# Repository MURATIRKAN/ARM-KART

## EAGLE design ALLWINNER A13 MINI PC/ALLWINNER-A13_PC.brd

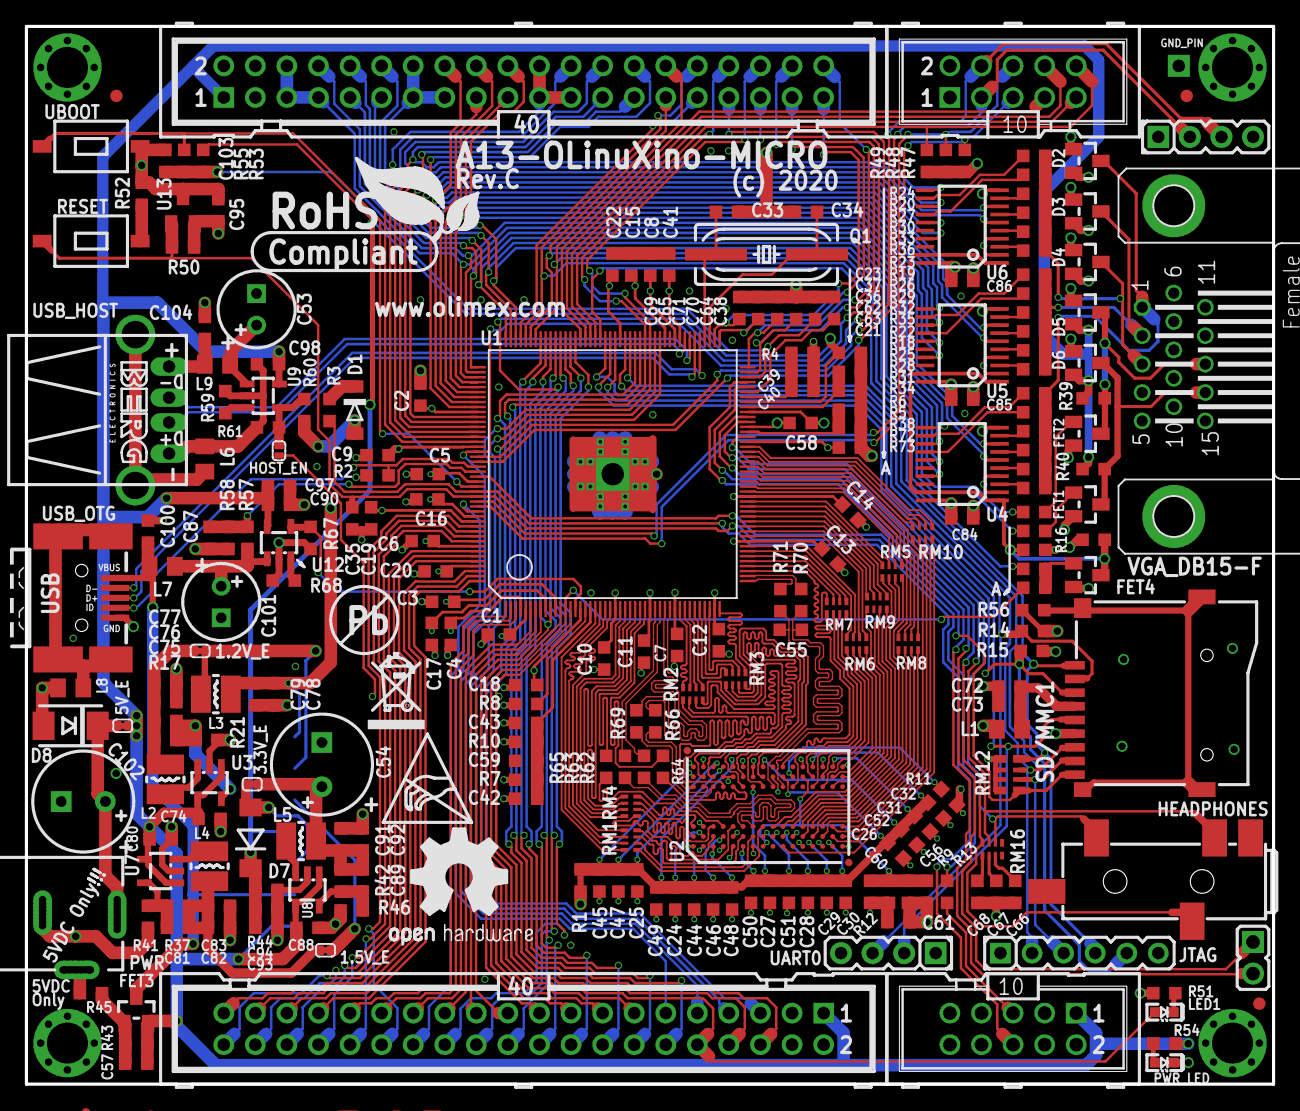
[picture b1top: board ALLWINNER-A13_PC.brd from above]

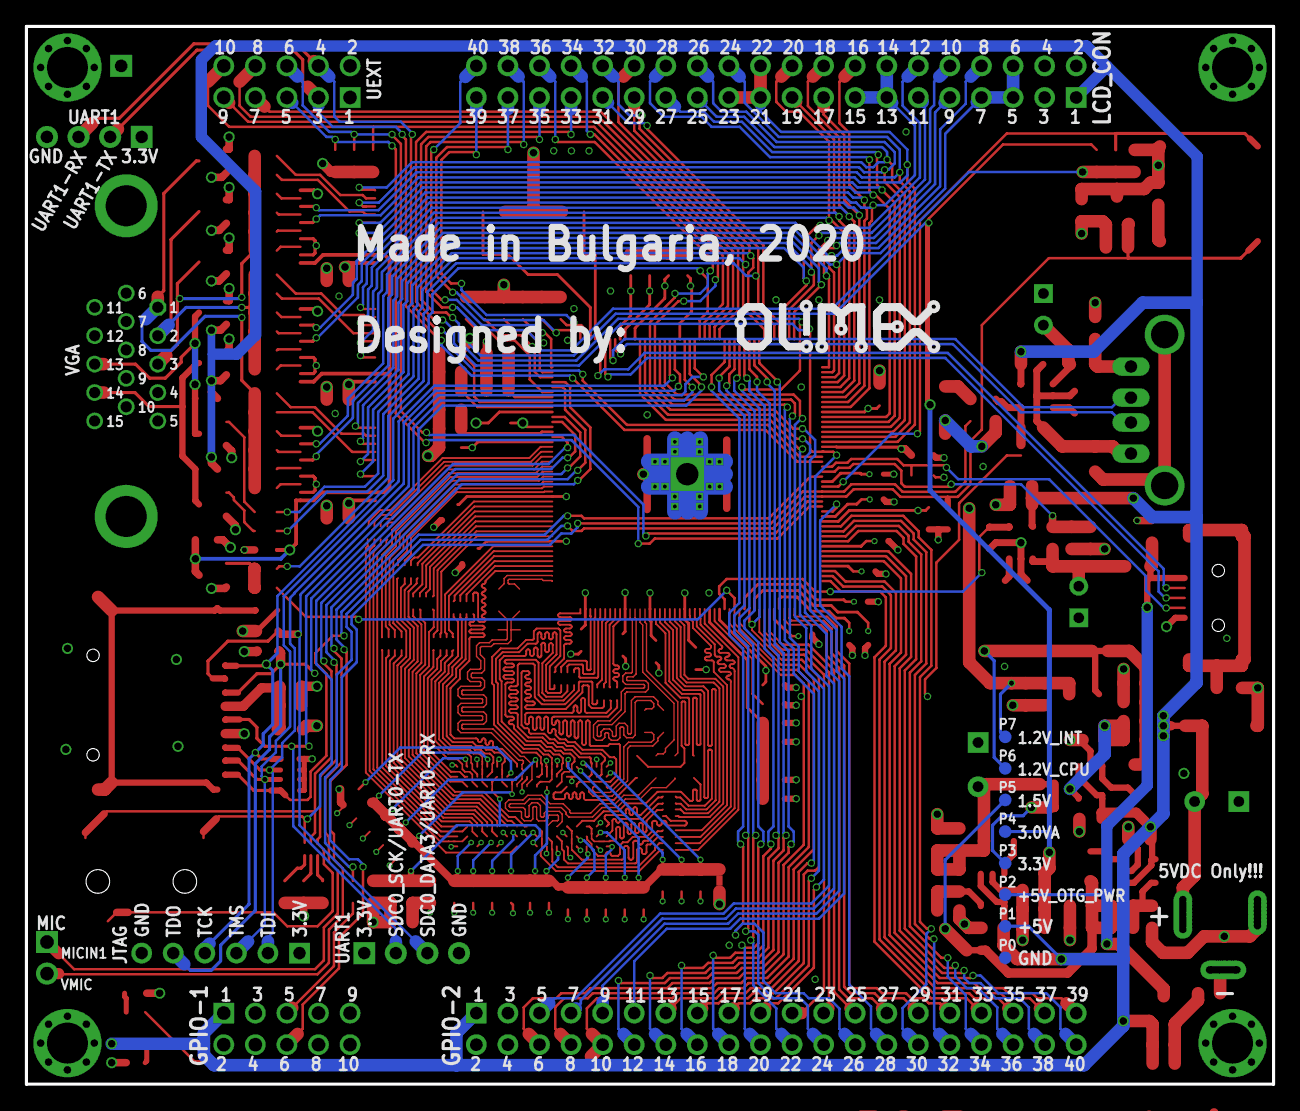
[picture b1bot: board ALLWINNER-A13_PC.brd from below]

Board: 4 copper layers, 100.3 x 85.1 mm, 261 parts (9 on the bottom side), 264 nets.

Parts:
1.2V_E, 1.5V_E, 3.3V_E, 5V_E: Close; SJ_1_SMALLER_CLOSE
C1, C11, C13, C15, C16, C17, C18, C19, C20, C21, C22, C24, C25, C26, C28, C29, C30, C31, C32, C37, C39, C41, C42, C43, C44, C45, C46, C47, C48, C49, C51, C52, C56, C57, C58, C59, C60, C63, C66, C67, C68, C84, C85, C86, C90, C95, C100, C104: 100nF; C0603_DWS
C2, C3, C7, C10, C23, C27, C50, C72, C73, C74, C76, C77, C80, C82, C83, C88, C91, C92, C93, C94, C97: 22uF/6.3V; C0603_DWS
C4, C5, C6, C8, C9, C12, C14, C36, C40, C62, C78, C98: 10uF/6.3V; C0603_DWS
C33, C34: 33pF; C0603_DWS
C35, C55: NA; C0603_DWS
C38: 1uF; C0603_DWS
C53, C101: 100uF/16V/LOWESR/105C/6.3x11mm_RM2.5; E2,5-6,3
C54: NA; E3,5-8
C61: NA(22uF/6.3V); C0603_DWS
C64, C65, C69, C70, C71, C79, C103: 1nF; C0603_DWS
C75, C81: 22pF; C0603_DWS
C87: NA(100nF); C0603_DWS
C89: 47pF; C0603_DWS
C102: 470uF/16V/105C; E3,5-8
D1: 1N5819(S4SOD-123); SOD-123
D2, D3, D4, D5, D6: BAT54S; SOT23C(BAT54S)
D7: 1N5819/SS14; MLL-41
D8: SMBJ6.0; DO214AA
FET1, FET2, FET4: BSS138; SOT23
FET3: IRLML6402; SOT23
GND_PIN: TESTPAD3; TEST_PAD40/70/SQUARE
GPIO-1: BH10S; ML10-MALE
GPIO-2: ML40
HEADPHONES: PJ-W47S-05D2-LF_V2; PJ-W47S-05D2-LF_5PIN_V2
HOST_EN: Open; SJ_1_SMALLER
JTAG: NA(HN1X6); HN1X6
L1, L6, L7, L8, L9: FB0805/600R/2A; L0805_5MIL_DWS
L2, L3, L4, L5: 2.2uH/1.5A/DCR<0.1R/CD32; CD32
LCD_CON: ML40
LED1: LED/GREEN/0603; LED-0603
MIC: NA(HN1x2); JP1
P0, P1, P2, P3, P4, P5, P6, P7: TESTPADTESTPAD_40-ROUND; TESTPAD_40-ROUND
PWR: YDJ-1136; PWR_JACK_UNI_MILLING
PWR_LED: LED/RED/0603; LED-0603
Q1: 24Mhz/HU49SM/20ppm/20pf; HC49/SMD2_THIN
R1: 0R(Board_Mounted); 0603_0R
R2, R3, R49, R57: 47k; R0603_5MIL_DWS
R4, R67: 200k/1%; R0603_5MIL_DWS
R5, R6, R52, R72: 51R; R0603_5MIL_DWS
R7, R10: 2k/1%; R0603_5MIL_DWS
R8, R11, R13: 240R/1%; R0603_5MIL_DWS
R9, R12, R16, R39, R40, R45: 1k/1%; R0603_5MIL_DWS
R14: NA(1M); R0603_5MIL_DWS
R15, R38, R43, R56, R60: 10k; R0603_5MIL_DWS
R17, R28, R29, R30: 2.2k/1%; R0603_5MIL_DWS
R18, R19, R20: 17.8k/1%; R0603_5MIL_DWS
R21: 1.5k/1%; R0603_5MIL_DWS
R22, R23, R24: 8.66k/1%; R0603_5MIL_DWS
R25, R26, R27: 4.32k/1%; R0603_5MIL_DWS
R31, R32, R33: 1.05k/1%; R0603_5MIL_DWS
R34, R35, R36: 549R/1%; R0603_5MIL_DWS
R37: 4.99k/1%; R0603_5MIL_DWS
R41: 3.3k/1%; R0603_5MIL_DWS
R42, R53, R58: 100k/1%; R0603_5MIL_DWS
R44, R47, R48, R51, R54: 2.2k; R0603_5MIL_DWS
R46: 22k/1%; R0603_5MIL_DWS
R50: 10k(NA); R0603_5MIL_DWS
R55: 6.8k/1%; R0603_5MIL_DWS
R59, R68: 13k/1%; R0603_5MIL_DWS
R61, R73: NA; R0603_5MIL_DWS
R62, R63, R64, R65, R66, R69, R70, R71: 22R; R0603_5MIL_DWS
RESET: T1107A(6x3.8x2.5mm); SW-TAKT_6X3.5_SMD
RM1, RM2, RM3, RM4, RM5, RM6, RM7, RM8, RM9, RM10, RM16: RA0805_(4X0402)_22R; R_MATRIX_4_0402_25X625
RM12: RA1206_(4X0603)_4B8_100K; R_MATRIX_4
SD/MMC1: MICRO_SD/TFC-WPAPR-08; TFC-WPAPR-08
U1: A13; TQFP176
U2: H5TQ2G63BFR; FBGA96@1
U3, U7, U8: SY8008C(AA)C; SOT23-5
U4, U5, U6: SN74ALVC244; PW
U9, U12: SY6280; SOT23-5
U13: MCP130T-300I/TT; SOT23
U$1, U$2, U$3: FIDUCIAL; FIDUCIAL-1X3
U$5: LOGO-OPENHARDWARE_8X8
U$8: OLIMEX1_V
U$9: PB
U$10: ESD_SYMBOL
U$11: RECYCLE_BIN1/8
U$12: ROHS
UART0: NA(HN1X4); HN1X4
UART1: HN1X4
UBOOT: T1107A(6x3.8x2.5mm); SW-TAKT_6X3.5_SMD
UEXT: BH10S; ML10-MALE
USB_HOST: USB_A; USB_PN87520_HOST_PTH
USB_OTG: USB-OTG; USB_MINI_9PIN
VGA_DB15-F: VGA15; DB15-F_22MM

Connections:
+5V: 5V_E.2, C57.1, C74.1, C80.1, C88.1, C90.1, C97.1, C98.1, D5.2, D6.2, FET3.2, GPIO-1.1, GPIO-2.1, LCD_CON.1, P1.1, R39.2, R40.2, R43.2, R54.1, U3.1, U3.4, U7.1, U7.4, U8.1, U8.4, U9.5, U12.5
+5V_OTG_PWR: C100.1, FET3.3, L7.1, P2.1, USB_OTG.VBUS
A0: RM5.1.2, U2.N3
A1: RM6.3.2, U2.P7
A2: RM8.3.2, U2.P3
A3: RM8.4.2, U2.N2
A4: RM6.4.2, U2.P8
A5: RM8.2.2, U2.P2
A6: RM6.2.2, U2.R8
A7: RM10.2.2, U2.R2
A8: RM6.1.2, U2.T8
A9: RM10.4.2, U2.R3
A10: RM7.3.2, U2.L7
A11: RM9.4.2, U2.R7
A12: RM7.1.2, U2.N7
A13: RM8.1.2, U2.T3
BA0: RM5.2.2, U2.M2
BA1: RM7.2.2, U2.N8
BA2: RM5.3.2, U2.M3
CASN: RM9.1.2, U2.K3
CKE: RM7.4.2, U2.K9
CLK: C55.1, R71.1, U2.J7
CLKN: C55.2, R70.1, U2.K7
D0: RM1.1.2, U2.E3
D1: RM3.4.2, U2.F7
D2: RM1.2.2, U2.F2
D3: RM3.3.2, U2.F8
D4: RM1.4.2, U2.H3
D5: RM3.1.2, U2.H8
D6: RM1.3.2, U2.G2
D7: RM3.2.2, U2.H7
D8: RM2.3.2, U2.D7
D9: RM4.3.2, U2.C3
D10: RM2.1.2, U2.C8
D11: RM4.4.2, U2.C2
D12: RM2.4.2, U2.A7
D13: RM4.2.2, U2.A2
D14: RM2.2.2, U2.B8
D15: RM4.1.2, U2.A3
DDR3_A0: RM5.1.1, U1.64
DDR3_A1: RM6.3.1, U1.52
DDR3_A2: RM8.3.1, U1.66
DDR3_A3: RM8.4.1, U1.65
DDR3_A4: RM6.4.1, U1.51
DDR3_A5: RM8.2.1, U1.67
DDR3_A6: RM6.2.1, U1.54
DDR3_A7: RM10.2.1, U1.71
DDR3_A8: RM6.1.1, U1.55
DDR3_A9: RM10.4.1, U1.69
DDR3_A10: RM7.3.1, U1.48
DDR3_A11: RM9.4.1, U1.56
DDR3_A12: RM7.1.1, U1.50
DDR3_A13: RM8.1.1, U1.68
DDR3_A14: RM9.3.1, U1.57
DDR3_BA0: RM5.2.1, U1.63
DDR3_BA1: RM7.2.1, U1.49
DDR3_BA2: RM5.3.1, U1.61
DDR3_CAS: RM9.1.1, U1.59
DDR3_CK: R71.2, U1.45
DDR3_CKE: RM7.4.1, U1.47
DDR3_CK_N: R70.2, U1.46
DDR3_D0: RM1.1.1, U1.22
DDR3_D1: RM3.4.1, U1.40
DDR3_D2: RM1.2.1, U1.21
DDR3_D3: RM3.3.1, U1.41
DDR3_D4: RM1.4.1, U1.19
DDR3_D5: RM3.1.1, U1.44
DDR3_D6: RM1.3.1, U1.20
DDR3_D7: RM3.2.1, U1.42
DDR3_D8: RM2.3.1, U1.37
DDR3_D9: RM4.3.1, U1.25
DDR3_D10: RM2.1.1, U1.39
DDR3_D11: RM4.4.1, U1.24
DDR3_D12: RM2.4.1, U1.36
DDR3_D13: RM4.2.1, U1.26
DDR3_D14: RM2.2.1, U1.38
DDR3_D15: RM4.1.1, U1.27
DDR3_DM0: R64.2, U1.29
DDR3_DM1: R65.2, U1.28
DDR3_DQS0: R63.2, U1.31
DDR3_DQS0_N: R62.2, U1.32
DDR3_DQS1: R69.2, U1.33
DDR3_DQS1_N: R66.2, U1.34
DDR3_ODT: RM10.1.2, U2.K1
DDR3_ODTT: RM10.1.1, U1.72
DDR3_RAS: RM9.2.1, U1.58
DDR3_RST: RM10.3.2, U2.T2
DDR3_RSTT: RM10.3.1, U1.70
DDR3_WE: RM5.4.1, U1.60
DQM0: R64.1, U2.E7
DQM1: R65.1, U2.D3
DQS0: R63.1, U2.F3
DQS0_N: R62.1, U2.G3
DQS1: R69.1, U2.C7
DQS1_N: R66.1, U2.B7
DZQ: R8.2, U1.17
GND: C1.1, C2.1, C3.1, C4.1, C5.1, C6.1, C7.1, C8.1, C9.1, C10.1, C11.1, C12.1, C13.1, C14.1, C15.1, C16.1, C17.1, C18.1, C19.1, C20.1, C21.1, C22.1, C23.1, C24.2, C25.2, C26.2, C27.2, C28.2, C29.2, C30.2, C31.2, C32.2, C33.1, C34.1, C35.1, C36.1, C37.1, C38.1, C39.1, C40.1, C41.1, C43.1, C44.2, C45.2, C46.2, C47.2, C48.2, C49.2, C50.2, C51.2, C52.2, C53.-, C54.-, C58.1, C59.1, C60.1, C61.1, C62.1, C63.1, C64.1, C65.1, C66.1, C67.1, C68.1, C69.1, C70.1, C71.1, C72.1, C73.1, C74.2, C76.2, C77.2, C78.2, C79.2, C80.2, C82.2, C83.2, C84.2, C85.2, C86.2, C87.2, C88.2, C90.2, C91.2, C92.2, C93.2, C94.2, C95.2, C97.2, C98.2, C100.2, C101.-, C102.-, C103.2, C104.2, D2.1, D3.1, D4.1, D5.1, D6.1, D8.A, FET1.2, FET2.2, FET4.2, GND_PIN.P$1, GPIO-1.2, GPIO-1.4, GPIO-2.2, GPIO-2.4, JTAG.6, L6.1, L8.1, LCD_CON.2, LCD_CON.4, P0.1, PWR.-, PWR_LED.C, R4.2, R8.1, R10.1, R11.1, R12.1, R14.2, R21.2, R38.1, R41.2, R44.2, R46.2, R51.1, R52.2, R56.2, R58.1, R59.1, R61.1, R67.1, R68.1, SD/MMC1.6, U1.79, U1.GND_PAD, U1.P$2, U1.P$3, U1.P$4, U1.P$5, U1.P$6, U1.P$7, U1.P$8, U1.P$9, U1.P$10, U1.P$11, U1.P$12, U1.P$13, U1.P$14, U1.P$15, U1.P$16, U1.P$17, U1.P$18, U2.A9, U2.B1, U2.B3, U2.B9, U2.D1, U2.D8, U2.E1, U2.E2, U2.E8, U2.F9, U2.G1, U2.G8, U2.G9, U2.J2, U2.J8, U2.L2, U2.M1, U2.M9, U2.P1, U2.P9, U2.T1, U2.T9, U3.2, U4.2, U4.4, U4.10, U5.2, U5.4, U5.10, U6.2, U6.4, U6.10, U7.2, U8.2, U9.2, U12.2, U13.3, UART0.4, UART1.4, UBOOT.P$1, UEXT.2, USB_HOST.4, USB_OTG.GND, VGA_DB15-F.5, VGA_DB15-F.6, VGA_DB15-F.7, VGA_DB15-F.8, VGA_DB15-F.10, VGA_DB15-F.GND1, VGA_DB15-F.GND2
LCD_CLK: LCD_CON.31, U1.129
LCD_D2: LCD_CON.21, LCD_CON.22, LCD_CON.23, U1.148, U6.6
LCD_D3: LCD_CON.24, U1.147, U6.8
LCD_D4: LCD_CON.25, U1.146, U6.11
LCD_D5: LCD_CON.26, U1.145, U6.13
LCD_D6: LCD_CON.27, U1.144, U6.15
LCD_D7: LCD_CON.28, U1.143, U6.17
LCD_D10: LCD_CON.13, LCD_CON.14, LCD_CON.15, U1.141, U5.6
LCD_D11: LCD_CON.16, U1.140, U5.8
LCD_D12: LCD_CON.17, U1.139, U5.11
LCD_D13: LCD_CON.18, U1.138, U5.13
LCD_D14: LCD_CON.19, U1.137, U5.15
LCD_D15: LCD_CON.20, U1.136, U5.17
LCD_D18: LCD_CON.5, LCD_CON.6, LCD_CON.7, U1.135, U4.6
LCD_D19: LCD_CON.8, U1.134, U4.8
LCD_D20: LCD_CON.9, U1.133, U4.11
LCD_D21: LCD_CON.10, U1.132, U4.13
LCD_D22: LCD_CON.11, U1.131, U4.15
LCD_D23: LCD_CON.12, U1.130, U4.17
LCD_DE: LCD_CON.32, R72.2, U1.128
LCD_HSYNC: LCD_CON.29, R6.1, U1.127
LCD_VSYNC: LCD_CON.30, R5.1, U1.126
LRADC: C64.2, C103.1, R53.2, R55.1, U1.86
MICIN1: MIC.1, U1.84
unnamed: C62.2, C63.2, U1.75
unnamed: FET4.1, R72.1, R73.1
unnamed: 5V_E.1, C102.+, D8.C, PWR.+
unnamed: L2.1, U3.3
unnamed: R56.1, SD/MMC1.10, SD/MMC1.11, SD/MMC1.12, SD/MMC1.13
unnamed: C57.2, FET3.1, R43.1, R45.2
unnamed: L4.1, U7.3
unnamed: C36.2, C37.2, U1.80
unnamed: D1.C, R3.2
unnamed: PWR.--, R45.1
unnamed: FET1.1, R5.2
unnamed: C38.2, U1.83
unnamed: C39.2, C40.2, R4.1, U1.82
unnamed: FET2.1, R6.2
unnamed: C101.+, L7.2, R57.2, U12.1
unnamed: 1.5V_E.1, C81.1, C82.1, C83.1, L4.2, R37.1
unnamed: C81.2, R37.2, R41.1, U7.5
unnamed: R33.1, U6.5
unnamed: L6.2, USB_HOST.P$1, USB_HOST.P$2
unnamed: 1.2V_E.1, C75.1, C76.1, C77.1, L2.2, R17.1
unnamed: HOST_EN.2, R60.2, R61.2, U9.4
unnamed: HEADPHONES.2, RM16.3.2, U1.74
unnamed: HEADPHONES.5, RM16.2.2, U1.77
unnamed: HEADPHONES.3, RM16.1.2, U1.78
unnamed: C66.2, RM16.3.1
unnamed: C67.2, RM16.2.1
unnamed: GPIO-1.5, R13.2
unnamed: C56.2, C60.2, R9.1, R12.2, U2.H1, U2.M8
unnamed: C75.2, R17.2, R21.1, U3.5
unnamed: LED1.C, R51.2
unnamed: C68.2, RM16.1.1
unnamed: R52.1, RESET.P$1
unnamed: L5.1, U8.3
unnamed: 3.3V_E.1, C54.+, C89.1, C91.1, C92.1, L5.2, R42.1
unnamed: C89.2, R42.2, R46.1, U8.5
unnamed: R68.2, U12.3
unnamed: R59.2, U9.3
unnamed: R36.1, U6.3
unnamed: R27.1, U6.9
unnamed: R30.1, U6.7
unnamed: R20.1, U6.14
unnamed: R24.1, U6.12
unnamed: C104.1, L9.2, USB_HOST.1
unnamed: C53.+, L9.1, U9.1
unnamed: R26.1, U5.9
unnamed: R29.1, U5.7
unnamed: PWR_LED.A, R54.2
unnamed: R32.1, U5.5
unnamed: R35.1, U5.3
unnamed: R19.1, U5.14
unnamed: R23.1, U5.12
unnamed: R25.1, U4.9
unnamed: R28.1, U4.7
unnamed: R31.1, U4.5
unnamed: R34.1, U4.3
unnamed: R18.1, U4.14
unnamed: R22.1, U4.12
unnamed: L8.2, USB_OTG.GND1, USB_OTG.GND2, USB_OTG.GND3, USB_OTG.GND4
NMI_N: GPIO-1.6, R3.1, U1.158
PIN4/TWI0-SCK: GPIO-2.5, U1.101
PIN5/TWI0-SDA: GPIO-2.7, U1.102
PIN6/PWM0: GPIO-2.9, LCD_CON.36, U1.103
PIN7: GPIO-2.11, LCD_CON.33, U1.150
PIN8: GPIO-2.13, LCD_CON.34, U1.104
PIN9: GPIO-2.15, LCD_CON.35, U1.10
PIN10/TWI1-SCK: GPIO-2.17, U1.105
PIN11/TWI1-SDA: GPIO-2.19, U1.106
PIN12/NWE: GPIO-2.21, U1.8
PIN13/NALE: GPIO-2.23, U1.7
PIN14/NCLE: GPIO-2.25, U1.6
PIN15/NCE1: GPIO-2.27, U1.3
PIN16/NCE0: GPIO-2.29, U1.2
PIN17/NRE: GPIO-2.31, U1.1
PIN18/NRB0: GPIO-2.33, U1.176
PIN19/NRB1: GPIO-2.35, U1.175
PIN20/NDQ0: GPIO-2.37, U1.174
PIN21/NDQ1: GPIO-2.39, U1.172
PIN22/NDQ2: GPIO-2.40, U1.171
PIN23/NDQ3: GPIO-2.38, U1.170
PIN24/NDQ4: GPIO-2.36, U1.168
PIN25/NDQ5: GPIO-2.34, U1.167
PIN26/NDQ6: GPIO-2.32, U1.166
PIN27/NDQ7: GPIO-2.30, U1.165
PIN28/NDQS: GPIO-2.28, U1.162
PIN29: GPIO-2.26, U1.118
PIN30: GPIO-2.24, U1.119
PIN31: GPIO-2.22, U1.120
PIN32: GPIO-2.20, U1.121
PIN33: GPIO-2.18, U1.122
PIN34: GPIO-2.16, U1.123
PIN35: GPIO-2.14, U1.124
PIN36: GPIO-2.12, U1.125
PIN37/LED1: GPIO-2.10, LED1.A, U1.12
PIN38/VGA_DIS: GPIO-2.8, R73.2, U1.13
PIN39/USBH_EN: GPIO-2.6, HOST_EN.1, U1.14
RASN: RM9.2.2, U2.J3
RESET_N: C35.2, R13.1, R50.1, RESET.P$2, U1.159, U13.1
SD0CARD-DETECT: RM12.1.1, SD/MMC1.9, U1.155
SDC0_CMD: JTAG.5, R15.1, SD/MMC1.3, U1.111
SDC0_DATA0: JTAG.2, RM12.3.1, SD/MMC1.7, U1.108
SDC0_DATA1: JTAG.3, RM12.2.1, SD/MMC1.8, U1.107
SDC0_DATA2: JTAG.4, RM12.4.1, SD/MMC1.1, U1.113
SDC0_DATA3: R14.1, SD/MMC1.2, U1.112, UART0.3
SDC0_SCK: SD/MMC1.5, U1.110, UART0.2
SD_VCC: C72.2, C73.2, L1.2, SD/MMC1.4
SPI2_CLK: U1.115, UEXT.9
SPI2_CS0: R49.1, U1.114, UEXT.10
SPI2_MISO: U1.117, UEXT.7
SPI2_MOSI: U1.116, UEXT.8
SVREF: C42.2, C43.2, C59.2, R7.1, R10.2, U1.18
TPX1: C65.2, LCD_CON.37, U1.89
TPX2: C70.2, LCD_CON.38, U1.87
TPY1: C69.2, LCD_CON.39, U1.90
TPY2: C71.2, LCD_CON.40, U1.88
TWI2_SCK: R47.1, U1.161, UEXT.5
TWI2_SDA: R48.1, U1.160, UEXT.6
UART1_RX: U1.151, UART1.3, UEXT.4
UART1_TX: U1.152, UART1.2, UEXT.3
UBOOT: R55.2, U1.157, UBOOT.P$2
UDM0: U1.93, USB_OTG.D-
UDM1: U1.95, USB_HOST.2
UDP0: U1.94, USB_OTG.D+
UDP1: U1.96, USB_HOST.3
USB0-DRV: R67.2, U1.15, U12.4
USB0-IDDET: R2.2, U1.153, USB_OTG.ID
USB0-VBUSDET: C87.1, R57.1, R58.2, U1.154
V+: 1.5V_E.2, C10.2, C11.2, C12.2, C13.2, C14.2, C42.1, C56.1, C61.2, P5.1, R1.1, R7.2, R9.2, U1.23, U1.30, U1.43, U1.53, U1.62
VCC: 3.3V_E.2, C1.2, C2.2, C15.2, C16.2, C41.2, C58.2, C84.1, C85.1, C86.1, C95.1, D1.A, D2.2, D3.2, D4.2, D7.A, GPIO-1.3, GPIO-2.3, JTAG.1, L1.1, LCD_CON.3, P3.1, R2.1, R15.2, R16.2, R47.2, R48.2, R49.2, R50.2, R60.1, RM12.1.2, RM12.2.2, RM12.3.2, RM12.4.2, U1.5, U1.76, U1.97, U1.100, U1.142, U1.163, U4.20, U5.20, U6.20, U13.2, UART0.1, UART1.1, UEXT.1
VCC/2: 1.2V_E.2, C3.2, C4.2, C5.2, C6.2, C17.2, C18.2, C19.2, C20.2, L3.1, P6.1, U1.4, U1.9, U1.11, U1.16, U1.156, U1.164, U1.169, U1.173
VCCINT: C7.2, C8.2, C9.2, C21.2, C22.2, C78.1, C79.1, L3.2, P7.1, U1.35, U1.73, U1.98, U1.109, U1.149
VDD.: C24.1, C25.1, C26.1, C27.1, C28.1, C29.1, C30.1, C31.1, C32.1, C44.1, C45.1, C46.1, C47.1, C48.1, C49.1, C50.1, C51.1, C52.1, R1.2, U2.A1, U2.A8, U2.B2, U2.C1, U2.C9, U2.D2, U2.D9, U2.E9, U2.F1, U2.G7, U2.H2, U2.H9, U2.K2, U2.K8, U2.N1, U2.N9, U2.R1, U2.R9
VGA_B: D4.3, R20.2, R24.2, R27.2, R30.2, R33.2, R36.2, VGA_DB15-F.3
VGA_CTRL: FET4.3, R16.1, R38.2, U4.1, U4.19, U5.1, U5.19, U6.1, U6.19
VGA_G: D3.3, R19.2, R23.2, R26.2, R29.2, R32.2, R35.2, VGA_DB15-F.2
VGA_HSYNC: D5.3, FET2.3, R39.1, VGA_DB15-F.13
VGA_R: D2.3, R18.2, R22.2, R25.2, R28.2, R31.2, R34.2, VGA_DB15-F.1
VGA_VSYNC: D6.3, FET1.3, R40.1, VGA_DB15-F.14
VMIC: MIC.2, U1.85
VPP: C23.2, C93.1, C94.1, D7.K, P4.1, R44.1, R53.1, U1.81
WEN: RM5.4.2, U2.L3
XTALI: C33.2, Q1.2, U1.92
XTALO: C34.2, Q1.1, U1.91
ZQ: R11.2, U2.L8

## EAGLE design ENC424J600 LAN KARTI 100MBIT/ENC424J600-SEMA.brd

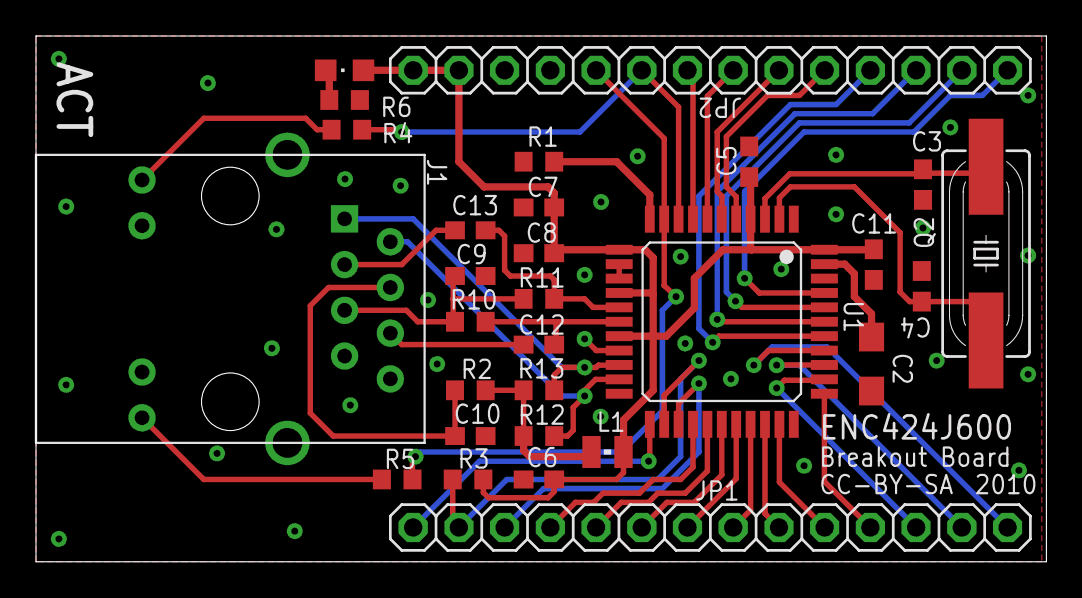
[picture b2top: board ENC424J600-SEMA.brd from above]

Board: 2 copper layers, 56.1 x 29.2 mm, 30 parts (1 on the bottom side), 42 nets.

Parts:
C2: 10uF; SMC_A
C3, C4: 27pf; C0603
C5, C6, C7, C8, C11: 0.1uF; C0603
C9, C10: 0.01uF; C0603
C12, C13: 6.8nF; C0603
J1: HR911105A
JP1, JP2: 1X14
L1: WE-KI_0805_B
PWR: LED-805
Q2: 25Mhz; HC49UP
R1: 12.4K 1%; R0603
R2: 10R, 1/12W, 1%; R0603
R3: 100K; R0603
R4, R5: 1K1; R0603
R6: 1k1; R0603
R10, R11, R12, R13: 49R9 1%; R0603
U1: ENC424J600; TQFP44
U$2: DP_LOGO

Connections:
3V3: C5.1, C6.1, C7.1, C8.1, C11.1, JP2.1, JP2.2, L1.1, PWR.A, R3.1, U1.P4, U1.P12, U1.P15, U1.P18, U1.P44
ACTIVITY: J1.9, R4.2
AD0: JP2.11, U1.P38
AD1: JP2.12, U1.P39
AD2: JP2.13, U1.P40
AD3: JP2.14, U1.P41
AD4: JP2.10, U1.P5
AD5: JP2.9, U1.P6
AD6: JP2.8, U1.P7
AD7: JP2.7, U1.P8
AD8: JP1.3, U1.P25
AD9: JP1.4, U1.P26
AD10: JP1.5, U1.P27
AD11: JP1.6, U1.P28
AD12: JP1.7, U1.P29
AD13: JP1.8, U1.P30
AD14: JP1.9, U1.P31
CCT: L1.2, R2.1, R12.2, R13.2
CLKOUT: JP1.1, U1.P23
DSFGDF: C12.1, R10.1, U1.P17
DSGDFSG: C13.1, R11.1, U1.P16
ETH-CS: JP1.11, U1.P34
ETH-INT: JP1.2, R3.2, U1.P24
ETH-MISO: JP1.12, U1.P35
ETH-MOSI: JP1.13, U1.P36
ETH-SCK: JP1.14, U1.P37
GND: C2.-, C3.2, C4.2, C5.2, C6.2, C7.2, C8.2, C9.2, C10.2, C11.2, J1.10, J1.11, J1.13, J1.14, JP2.3, JP2.4, R1.2, R6.1, U1.P1, U1.P13, U1.P14, U1.P19, U1.P22, U1.P33, U1.P42
LED_A: JP2.5, R5.1, U1.P10
LED_B: JP2.6, R4.1, U1.P9
LINK: J1.12, R5.2
unnamed: C2.+, U1.P43
unnamed: R1.1, U1.P11
unnamed: PWR.C, R6.2
unnamed: C3.1, Q2.1, U1.P3
unnamed: C4.1, Q2.2, U1.P2
PSPCFG0: JP1.10, U1.P32
RD+: C13.2, J1.3
RD-: C12.2, J1.6
RD-CT: C9.1, J1.5, R10.2, R11.2
TD+: J1.1, R13.1, U1.P20
TD-: J1.2, R12.1, U1.P21
TD-CT: C10.1, J1.4, R2.2

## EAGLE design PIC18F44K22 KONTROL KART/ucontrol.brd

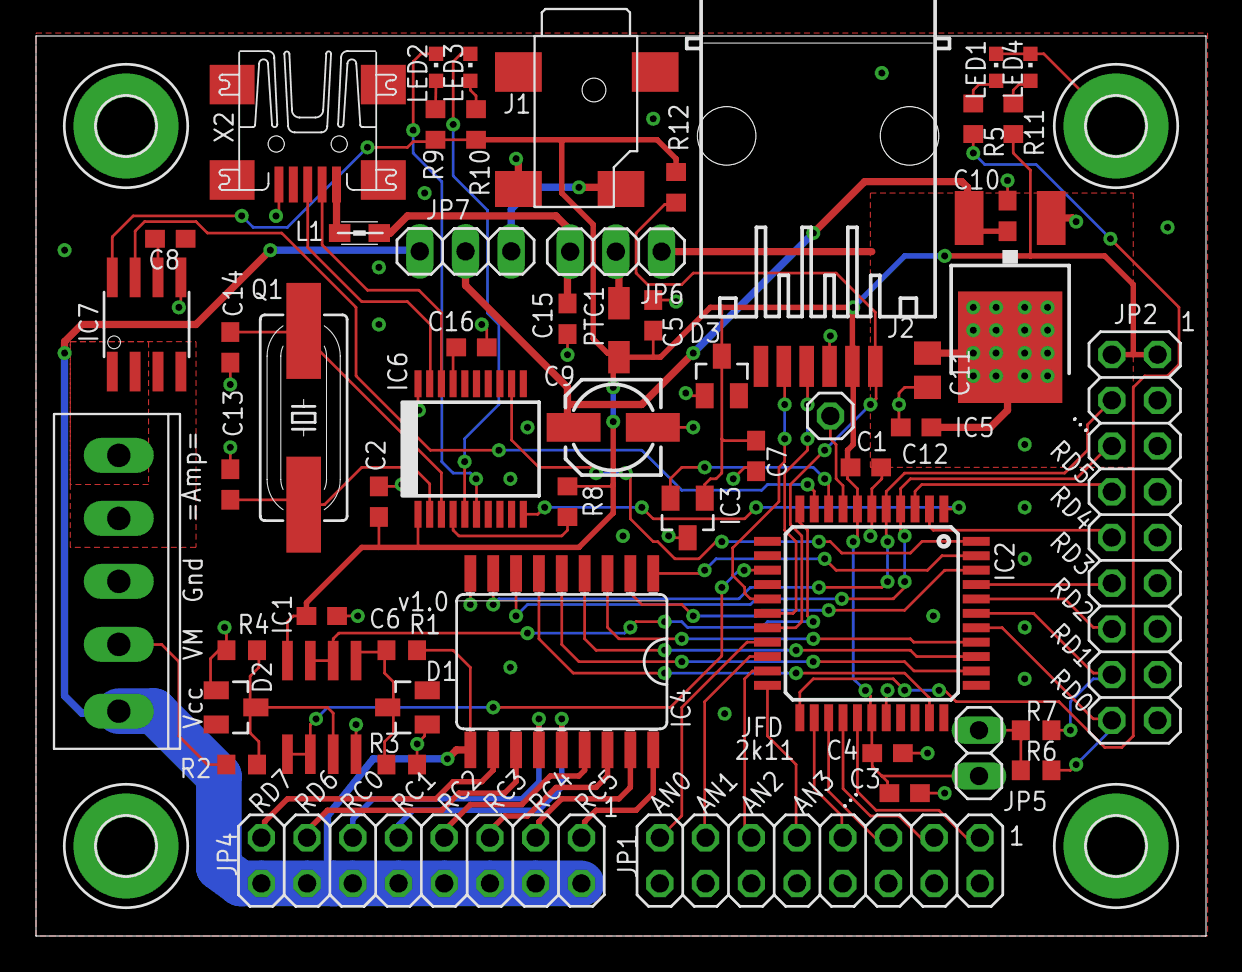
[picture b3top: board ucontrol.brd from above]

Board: 2 copper layers, 65.0 x 50.0 mm, 60 parts (0 on the bottom side), 69 nets.

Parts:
C1: 1u; C0603
C2, C3, C5, C6, C7, C10, C12: 100n; C0603
C4, C15: 10n; C0603
C8: 1n; C0603
C9: 22u; 153CLV-0505
C11: 10u; C0805
C13, C14: 18p; C0603
C16: 470n; C0603
D1, D2, D3: GSOT05-GS08; SOT23
H1, H2, H3, H4: MOUNT-PAD-ROUND3.2; 3,2-PAD
IC1: MCP6282; SO08
IC2: PIC18F44K22; TQFP44
IC3: LM60; SOT23
IC4: ULN2803; SO18
IC5: AP1117D5; DPACK
IC6: MCP2200; SSOP20
IC7: ACS714; SO08
J1: PJ-029-SMT; SMT
J2: 555077-1
JP1, JP4: 2X08
JP2: 2X09
JP3: 1X01
JP5: 1X02
JP6, JP7: 1X03
L1: MI0805K400R-10; 0805
LED1, LED2, LED3, LED4: GRN; CHIPLED_0603
PTC1: MF-NSMF050-2; 1206
Q1: 12MHz; HC49UP
R1: 3k; R0603
R2: 9k1; R0603
R3, R4: 1k; R0603
R5, R9, R10, R11: 1k65; R0603
R6, R7, R8, R12: 10k; R0603
X1: OSTTE-5
X2: MINI-USB-UX60-MB-5ST; UX60-MB-5ST

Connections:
5VL: C11.1, C12.1, IC5.4, JP6.1
5VUSB: C15.1, JP6.3, L1.1
+5V: C1.1, C2.1, C3.1, C4.1, C5.1, C6.1, C7.1, D3.3, IC1.8, IC2.7, IC2.28, IC3.1, IC6.1, IC7.8, J2.2, JP2.1, JP2.2, JP5.1, PTC1.2, R8.2, R9.2, R10.2, R11.2, R12.2
ALIVE: IC2.23, R5.2
AMP: IC2.10, IC7.7
AN0: IC2.19, JP1.15
AN1: IC2.20, JP1.13
AN2: IC2.21, JP1.11
AN3: IC2.22, JP1.9
AN4: IC2.24, JP1.7
AN5: IC2.25, JP1.5
AN6: IC2.26, JP1.3
AN7: IC2.27, JP1.1
D+: IC6.19, X2.3
D-: IC6.18, X2.2
GND: C1.2, C2.2, C3.2, C4.2, C5.2, C6.2, C7.2, C8.1, C9.-, C10.2, C11.2, C12.2, C13.1, C14.1, C15.2, C16.2, D1.1, D2.1, D3.1, H1.B3,2, H2.B3,2, H3.B3,2, H4.B3,2, IC1.4, IC2.6, IC2.29, IC3.3, IC4.9, IC5.1, IC6.20, IC7.5, J1.2, J2.3, JP1.2, JP1.4, JP1.6, JP1.8, JP1.10, JP1.12, JP1.14, JP1.16, JP2.4, JP2.6, JP2.8, JP2.10, JP2.12, JP2.14, JP2.16, JP2.18, LED1.C, LED4.C, R3.1, R4.1, X1.3, X2.5
IS1: IC7.1, IC7.2, X1.1
IS2: IC7.3, IC7.4, X1.2
MCLR: IC2.18, J2.1, R12.1
unnamed: C13.2, IC6.2, Q1.2
unnamed: C14.2, IC6.3, Q1.1
unnamed: JP5.2, R6.2, R7.2
unnamed: LED4.A, R11.1
unnamed: JP6.2, PTC1.1
unnamed: LED1.A, R5.1
unnamed: L1.2, X2.1
unnamed: C8.2, IC7.6
unnamed: IC2.8, JP3.1
unnamed: D1.3, IC1.5, R1.1, R3.2
unnamed: C9.+, C10.1, IC5.3, JP7.2
unnamed: D2.3, IC1.3, R2.1, R4.2
unnamed: IC6.4, R8.1
unnamed: IC6.5, LED3.C
unnamed: IC6.6, LED2.C
unnamed: LED2.A, R9.1
unnamed: LED3.A, R10.1
unnamed: C16.1, IC6.17
unnamed: J1.1, JP7.3
P0: IC4.13, JP4.11
P1: IC4.14, JP4.9
P2: IC4.15, JP4.7
P3: IC4.16, JP4.5
P4: IC4.17, JP4.3
P5: IC4.18, JP4.1
PD6: IC4.12, JP4.13
PD7: IC4.11, JP4.15
PGC: IC2.16, J2.5
PGD: IC2.17, J2.4
RC0: IC2.32, IC4.6
RC1: IC2.35, IC4.5
RC2: IC2.36, IC4.4
RC3: IC2.37, IC4.3
RC4: IC2.42, IC4.2
RC5: IC2.43, IC4.1
RD0: IC2.38, JP2.17, R6.1
RD1: IC2.39, JP2.15, R7.1
RD2: IC2.40, JP2.13
RD3: IC2.41, JP2.11
RD4: IC2.2, JP2.9
RD5: IC2.3, JP2.7
RD6: IC2.4, IC4.7, JP2.5
RD7: IC2.5, IC4.8, JP2.3
RX: IC2.1, IC6.10
TEMP: IC2.9, IC3.2
TX: IC2.44, IC6.12
VCC: IC4.10, JP4.2, JP4.4, JP4.6, JP4.8, JP4.10, JP4.12, JP4.14, JP4.16, JP7.1, R1.2, X1.5
VMETER: R2.2, X1.4
VOLT1: IC1.6, IC1.7, IC2.11
VOLT2: IC1.1, IC1.2, IC2.14

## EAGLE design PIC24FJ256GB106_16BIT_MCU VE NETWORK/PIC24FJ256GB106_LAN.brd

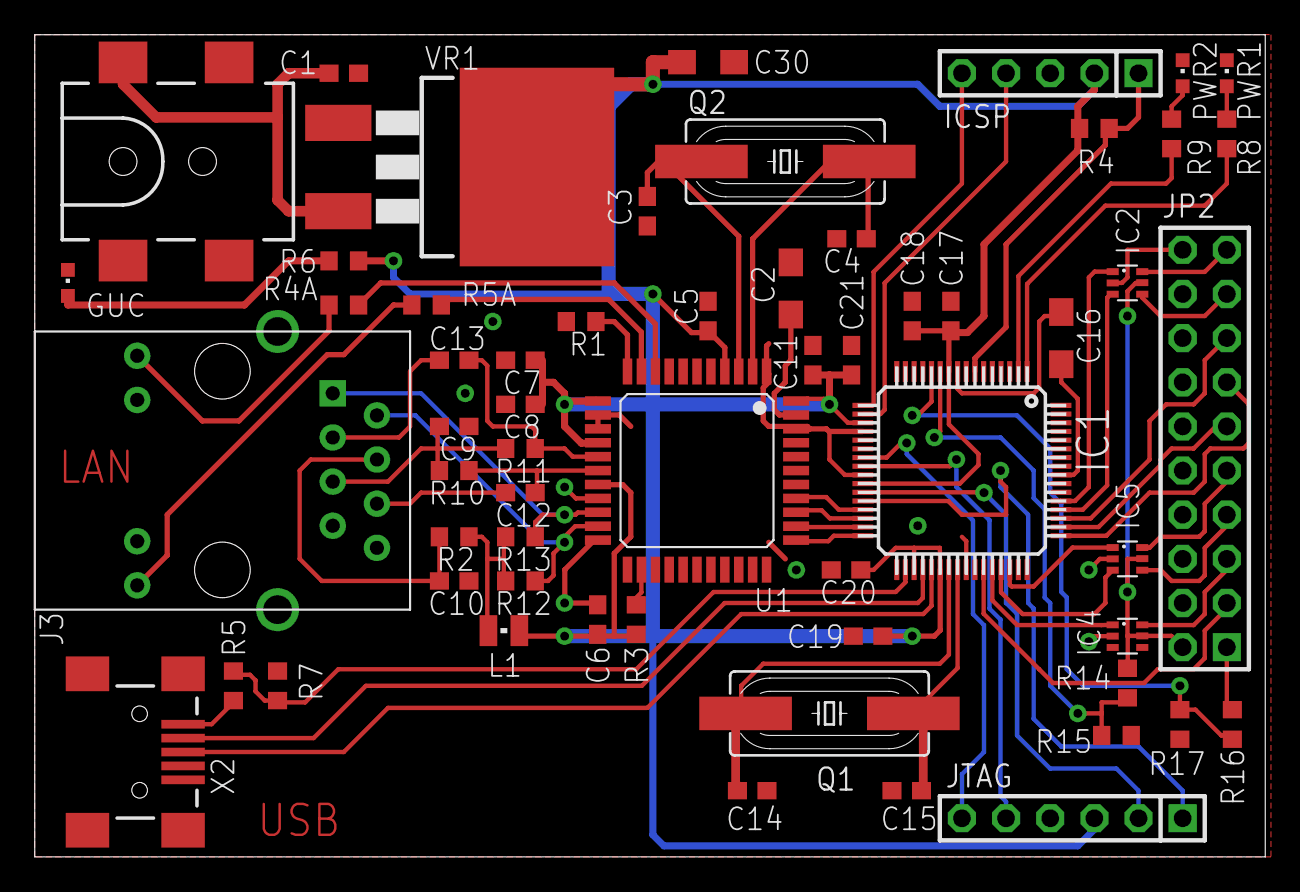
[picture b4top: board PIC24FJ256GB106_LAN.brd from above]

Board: 2 copper layers, 70.8 x 47.3 mm, 59 parts (0 on the bottom side), 62 nets.

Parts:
C1, C5, C6, C7, C8, C11, C17, C18, C19, C20, C21: 0.1uF; C0603
C2, C16, C30: 10uF; SMC_A
C3, C4, C14, C15: 27pf; C0603
C9, C10: 0.01uF; C0603
C12, C13: 6.8nF; C0603
GUC: CHIPLED_0603
IC1: PIC24FJ256GB106; TQFP64-10X10
IC2, IC4, IC5: NC7WZ07P6X; SC70-6
ICSP: 1X05
J1: POWER_JACKSMD; POWER_JACK_SMD
J3: HR911105A
JP2: 2X10
JTAG: 1X06
L1: WE-KI_0805_B
PWR1, PWR2: CHIPLED_0603
Q1, Q2: 25Mhz; HC49UP
R1: 12.4K 1%; R0603
R2: 10R, 1/12W, 1%; R0603
R3: 100K; R0603
R4, R4A, R5, R5A, R6, R7, R8, R9, R14, R15, R16, R17: 1K1; R0603
R10, R11, R12, R13: 49R9 1%; R0603
U1: ENC424J600; TQFP44
VR1: LD117AD2MTR; D2PACK
X2: USBSMD; USB-MINIB

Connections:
3V3: C5.1, C6.1, C7.1, C8.1, C11.1, C17.1, C18.1, C19.1, C20.1, C21.1, C30.+, IC1.10, IC1.19, IC1.26, IC1.35, IC1.38, ICSP.2, JTAG.3, L1.1, R3.1, R4.2, R6.1, U1.P4, U1.P12, U1.P15, U1.P18, U1.P44, VR1.2
CCT: L1.2, R2.1, R12.2, R13.2
DBGRQ: IC2.4, JP2.17
DBGRQ-UB: IC1.52, IC2.3
DGBACK: IC2.6, JP2.19
DGBACK-UB: IC1.53, IC2.1
DSFGDF: C12.1, R10.1, U1.P17
DSGDFSG: C13.1, R11.1, U1.P16
ETH-CS: IC1.32, U1.P34
ETH-INT: R3.2, U1.P24
ETH-MISO: IC1.31, U1.P35
ETH-MOSI: IC1.30, U1.P36
ETH-SCK: IC1.29, U1.P37
GND: C1.2, C2.-, C3.2, C4.2, C5.2, C6.2, C7.2, C8.2, C9.2, C10.2, C11.2, C14.2, C15.2, C16.-, C17.2, C18.2, C19.2, C20.2, C21.2, C30.-, GUC.C, IC1.9, IC1.20, IC1.25, IC1.41, IC2.2, IC4.2, IC5.2, ICSP.3, J1.GND, J1.P$4, J3.10, J3.11, J3.13, J3.14, JP2.4, JP2.6, JP2.8, JP2.10, JP2.12, JP2.14, JP2.16, JP2.18, JP2.20, JTAG.4, PWR1.C, PWR2.C, R1.2, R7.2, R15.1, R17.1, U1.P1, U1.P13, U1.P14, U1.P19, U1.P22, U1.P33, U1.P42, VR1.1, X2.GND
LED1: IC1.1, R8.1
LED2: IC1.2, R9.1
LED_A: R5A.1, U1.P10
LED_B: R4A.1, U1.P9
LED_LINK: J3.9, R4A.2
LED_STATUS: J3.12, R5A.2
MCLR: IC1.7, ICSP.1, R4.1
unnamed: C2.+, U1.P43
unnamed: R1.1, U1.P11
unnamed: C15.1, IC1.40, Q1.1
unnamed: C3.1, Q2.1, U1.P3
unnamed: C14.1, IC1.39, Q1.2
unnamed: PWR1.A, R8.2
unnamed: PWR2.A, R9.2
unnamed: C4.1, Q2.2, U1.P2
unnamed: C16.+, IC1.56
unnamed: IC1.34, R5.2, R7.1
unnamed: GUC.A, R6.2
NSRST: IC1.51, JP2.15
NTRST: IC1.43, JP2.3
PGC: IC1.17, ICSP.5
PGD: IC1.18, ICSP.4
PIC-TCK: IC1.27, JTAG.2
PIC-TDI: IC1.28, JTAG.1
PIC-TDO: IC1.24, JTAG.5
PIC-TMS: IC1.23, JTAG.6
RD+: C13.2, J3.3
RD-: C12.2, J3.6
RD-CT: C9.1, J3.5, R10.2, R11.2
RTCK: IC1.50, JP2.11
TCK: IC5.6, JP2.9
TCK-UB: IC1.46, IC5.1
TD+: J3.1, R13.1, U1.P20
TD-: J3.2, R12.1, U1.P21
TD-CT: C10.1, J3.4, R2.2
TDI: IC4.6, JP2.5
TDI-UB: IC1.44, IC4.1
TDO: IC1.49, JP2.13
TMS: IC5.4, JP2.7
TMS-UB: IC1.45, IC5.3
USBD+: IC1.37, X2.D+
USBD-: IC1.36, X2.D-
VBAT: C1.1, J1.VIN0, VR1.3
VREF: JP2.1, R16.1
VREFADC: IC1.12, R16.2, R17.2
VSUPPLY: IC2.5, IC4.5, IC5.5, JP2.2, R14.1
VSUPPLYADC: IC1.11, R14.2, R15.2
VUSB: R5.1, X2.VBUS

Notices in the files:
ALLWINNER A13 MINI PC/ALLWINNER-A13_PC.brd:
(c) 2020
ENC424J600 LAN KARTI 100MBIT/ENC424J600-SEMA.brd:
CC-BY-SA
parts and their libraries:
SparkFun-Capacitors: Licensing: Creative Commons ShareAlike 4.0 International - https://creativecommons.org/licenses/by-sa/4.0
